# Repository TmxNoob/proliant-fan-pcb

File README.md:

# Proliant fan PCB

Here you can find Kicad Projects for each server the mod supports.
The PCB-s arent fully tested yet so use at your own risk!

## dl380e

Proliant DL380e Gen8

## dl380p

Proliant DL380p Gen8
and all servers that have same kind of fan for example DL380e G8, but it is harder to install and then fans arent easily hot swappable.

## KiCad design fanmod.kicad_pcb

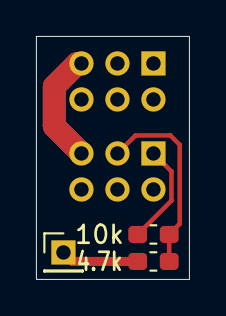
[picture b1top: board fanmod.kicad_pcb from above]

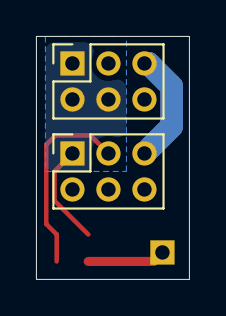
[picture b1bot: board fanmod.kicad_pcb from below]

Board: 2 copper layers, 8.5 x 13.5 mm, 5 parts (2 on the bottom side), 4 nets.

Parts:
J1: FAN_IN; PinSocket_2x03_P2.00mm_Vertical
J2: FAN_OUT; PinSocket_2x03_P2.00mm_Vertical
J4: COMM; PinHeader_1x01_P2.00mm_Vertical
R1: 4.7k; R_0603_1608Metric_Pad1.05x0.95mm_HandSolder
R2: 10k; R_0603_1608Metric_Pad1.05x0.95mm_HandSolder

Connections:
+12V: J1.5, J2.5
GND: J1.1, J1.2, J1.4, J2.1, R2.2
unnamed: J2.3, R1.2, R2.1
unnamed: J4.1, R1.1

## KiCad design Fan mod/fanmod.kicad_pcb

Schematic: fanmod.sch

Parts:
J1: FAN_IN; PinSocket_2x03_P2.00mm_Vertical_SMD
J2: FAN_OUT; PinHeader_2x03_P2.00mm_Vertical_SMD
J4: COMM; PinHeader_1x01_P2.00mm_Vertical
JP1: BYPASS; SolderJumper-2_P1.3mm_Open_RoundedPad1.0x1.5mm
R1: 1k; R_0603_1608Metric_Pad1.05x0.95mm_HandSolder
R2: 2k; R_0603_1608Metric_Pad1.05x0.95mm_HandSolder

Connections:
+12V: J1.1, J2.1
GND: J1.2, J2.2, JP1.2, R2.2
GROUND_LOOP: J1.4, J2.4, JP1.1
unnamed: J2.5, R1.2, R2.1
unnamed: J4.1, R1.1
ROTATION_DETECT: J1.6, J2.6

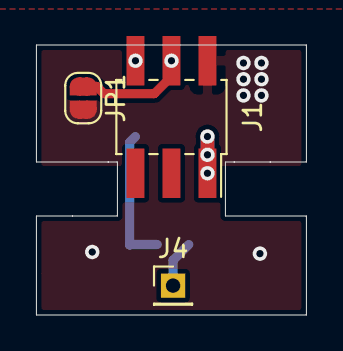
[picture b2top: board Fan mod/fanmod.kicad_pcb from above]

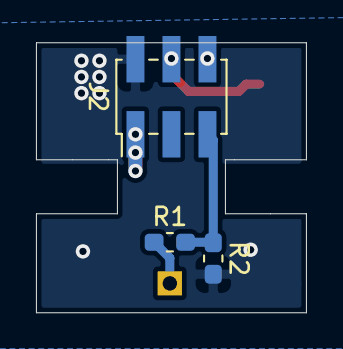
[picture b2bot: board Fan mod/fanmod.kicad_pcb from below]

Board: 2 copper layers, 15.0 x 15.0 mm, 6 parts (3 on the bottom side), 6 nets.

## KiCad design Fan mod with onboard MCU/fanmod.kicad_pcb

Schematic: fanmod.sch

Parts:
C1, C2: 10u; C_0603_1608Metric_Pad1.05x0.95mm_HandSolder
C3: C; C_0603_1608Metric_Pad1.05x0.95mm_HandSolder
D1: 3.3V; D_SOD-123
J1: FAN_IN; PinSocket_2x03_P2.00mm_Vertical_SMD
J2: FAN_OUT; PinHeader_2x03_P2.00mm_Vertical_SMD
J3: Conn_01x05; PinHeader_1x05_P1.27mm_Horizontal
J4: COMM; PinHeader_1x01_P2.00mm_Vertical
JP1: PROXY; SolderJumper-2_P1.3mm_Open_RoundedPad1.0x1.5mm
R1: 200R 0.5W; R_1210_3225Metric_Pad1.42x2.65mm_HandSolder
U1: LM1117-3.3; SOT-223-3_TabPin2
U2: ATtiny10-TS; SOT-23-6

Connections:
+3V3: C2.1, D1.1, J3.1, R1.2, U1.2, U2.5
+12V: C1.1, J1.1, J2.1, R1.1, U1.3
COMM: J4.1, JP1.1, U2.4
GROUND_LOOP: C1.2, C2.2, C3.2, D1.2, J1.2, J1.4, J2.2, J3.5, U1.1, U2.2
MCU_RESET: C3.1, J1.5, J3.4, U2.6
PROG_CLK: J1.6, J2.6, J3.3, U2.3
PROG_DATA: J2.5, J3.2, JP1.2, U2.1

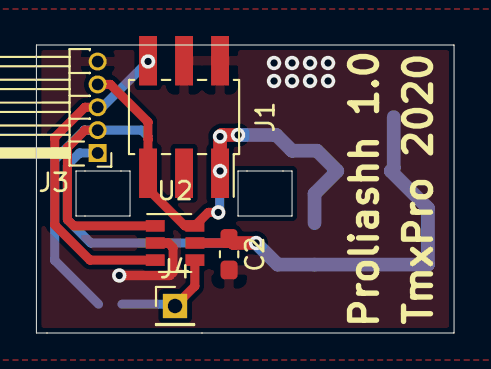
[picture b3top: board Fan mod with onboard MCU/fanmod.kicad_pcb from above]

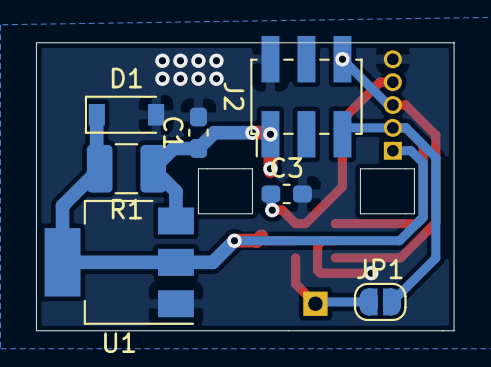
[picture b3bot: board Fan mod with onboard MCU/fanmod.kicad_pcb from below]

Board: 2 copper layers, 23.2 x 16.0 mm, 12 parts (7 on the bottom side), 7 nets.

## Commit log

2020-05-27 Add source
2020-06-02 Changed notch size so will fit better
2020-06-09 Split up different versions
2020-06-13 board v2.0
2020-06-13 dl380e board 2.0
2020-06-17 Add labels
2020-06-24 Edit README
2020-06-24 Edit master to only have README.md
2020-06-24 Add warning
